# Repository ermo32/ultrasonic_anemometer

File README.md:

# Ultrasonic Anemometer

This project is about the development of an ultrasonic anemometer. Classical mechanical anemometers
has a disadvantage of a mechanical construction. This anemometer is based on the time of flight of
an ultrasonic pulse. 

## Getting Started

The project consists of a hardware and a software part. A microchip DSPIC33 is used as processing unit. On the board, the analog part consist of analog switches and 
operational amplifiers (OPAMPs).

### Prerequisities

What things you need to install the software and how to install them

```
Give examples
```

### Installing

A step by step series of examples that tell you have to get a development env running

Say what the step will be

```
Give the example
```

And repeat

```
until finished
```

End with an example of getting some data out of the system or using it for a little demo

## Running the tests

Explain how to run the automated tests for this system

### Break down into end to end tests

Explain what these tests test and why

```
Give an example
```

### And coding style tests

Explain what these tests test and why

```
Give an example
```

## Deployment

Add additional notes about how to deploy this on a live system

## Built With

* Dropwizard - Bla bla bla
* Maven - Maybe
* Atom - ergaerga

## Contributing

Please read [CONTRIBUTING.md](https://gist.github.com/PurpleBooth/b24679402957c63ec426) for details on our code of conduct, and the process for submitting pull requests to us.

## Versioning

We use [SemVer](http://semver.org/) for versioning. For the versions available, see the [tags on this repository](https://github.com/your/project/tags). 

## Authors

* **Billie Thompson** - *Initial work* - [PurpleBooth](https://github.com/PurpleBooth)

See also the list of [contributors](https://github.com/your/project/contributors) who participated in this project.

## License

This project is licensed under the MIT License - see the [LICENSE.md](LICENSE.md) file for details

## Acknowledgments

* Hat tip to anyone who's code was used
* Inspiration
* etc

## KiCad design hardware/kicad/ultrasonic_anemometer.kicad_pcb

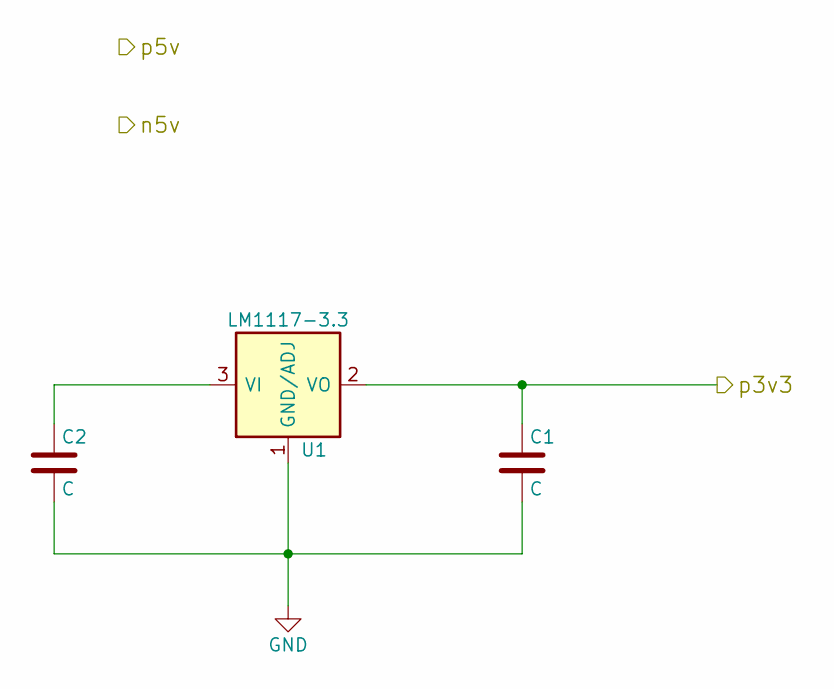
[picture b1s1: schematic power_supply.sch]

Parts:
C1, C2: C; C_0805_HandSoldering
U1: LM1117-3.3; SOT-223

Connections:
/Digital/p3v3: C1.1, U1.2 (VO), U1.4 (VO); also elsewhere on the board
GND: C1.2, C2.2, U1.1 (GND/ADJ); also elsewhere on the board
unnamed: C2.1, U1.3 (VI)

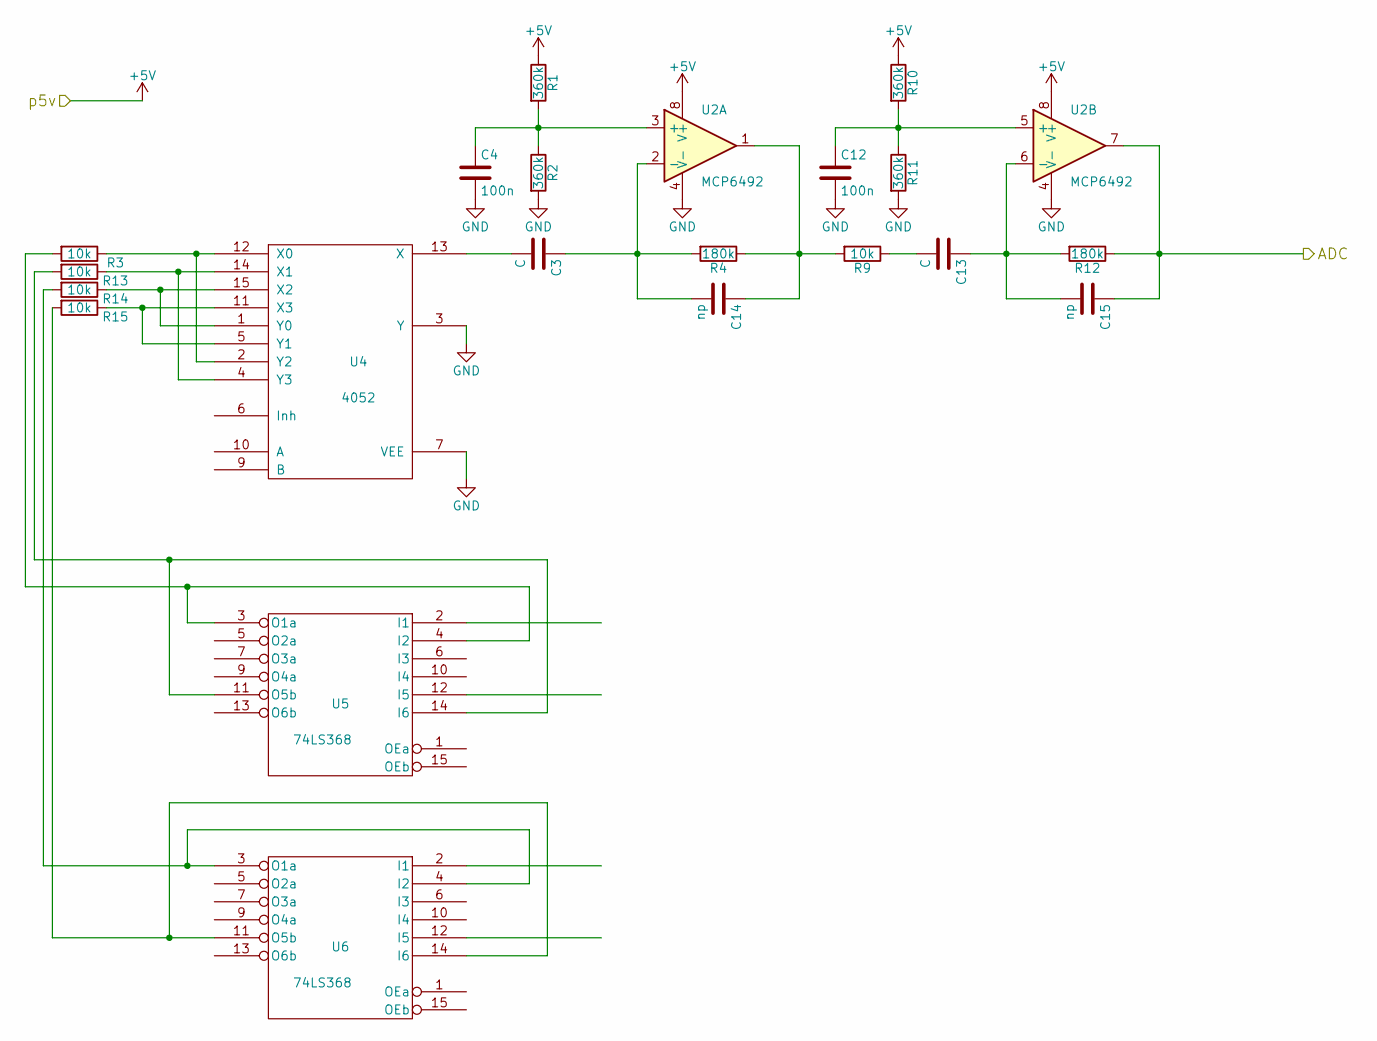
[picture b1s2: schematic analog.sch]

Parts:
C3, C13: C; C_0805_HandSoldering
C4, C12: 100n; C_0805_HandSoldering
C14, C15: np; C_0805_HandSoldering
R1, R2, R10, R11: 360k; R_0805_HandSoldering
R3, R9, R13, R14, R15: 10k; R_0805_HandSoldering
R4, R12: 180k; R_0805_HandSoldering
U2: MCP6492; SOIC-8_3.9x4.9mm_Pitch1.27mm
U4: 4052; DIP-16_W7.62mm_LongPads
U5, U6: 74LS368; DIP-16_W7.62mm_LongPads

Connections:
+5V: R1.1, R10.1, U2.8 (V+)
/Analog/ADC: C15.1, R12.1, U2.7; also elsewhere on the board
GND: C4.2, C12.2, R2.2, R11.2, U2.4 (V-), U4.3 (Y), U4.7 (VEE), U5.8 (GND), U6.8 (GND); also elsewhere on the board
unnamed: C3.2, U4.13 (X)
unnamed: C4.1, R1.2, R2.1, U2.3 (+)
unnamed: C12.1, R10.2, R11.1, U2.5 (+)
unnamed: C13.1, C15.2, R12.2, U2.6 (-)
unnamed: C13.2, R9.1
unnamed: C14.1, R4.1, R9.2, U2.1
unnamed: C3.1, C14.2, R4.2, U2.2 (-)
unnamed: R3.1, U4.2 (Y2), U4.12 (X0)
unnamed: R3.2, U5.3 (O1a), U5.4 (I2)
unnamed: R13.1, U4.4 (Y3), U4.14 (X1)
unnamed: R13.2, U5.11 (O5b), U5.14 (I6)
unnamed: R14.1, U4.1 (Y0), U4.15 (X2)
unnamed: R14.2, U6.3 (O1a), U6.4 (I2)
unnamed: R15.1, U4.5 (Y1), U4.11 (X3)
unnamed: R15.2, U6.11 (O5b), U6.14 (I6)
VCC: U5.16 (VCC), U6.16 (VCC)
VDD: U4.16 (VDD)
VSS: U4.8 (VSS)

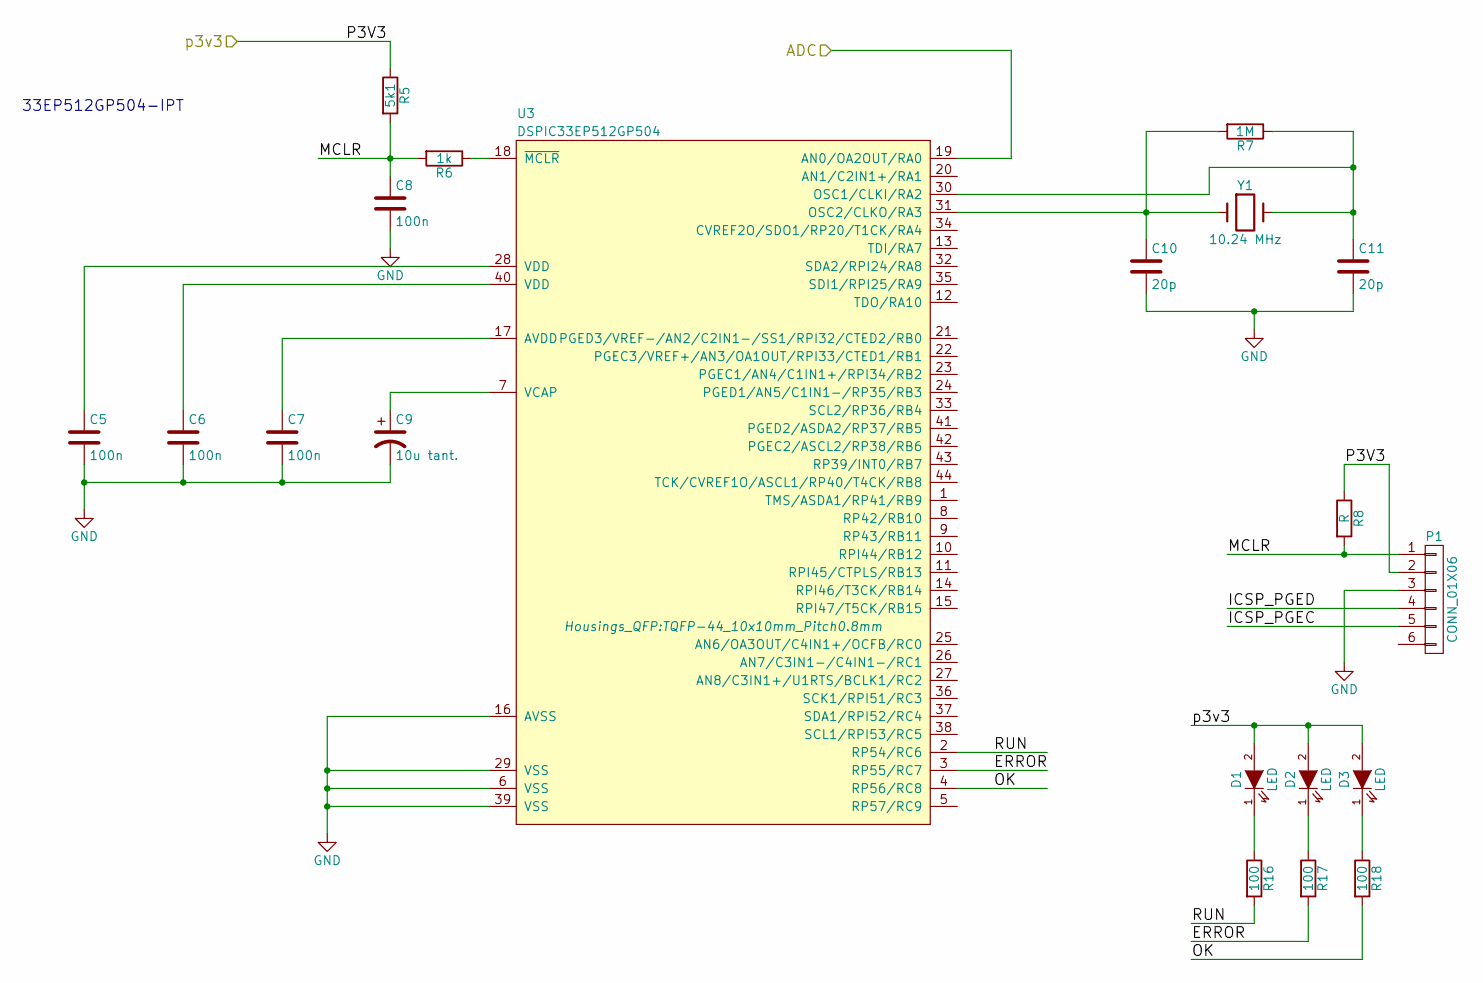
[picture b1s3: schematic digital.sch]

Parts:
C5, C6, C7, C8: 100n; C_0805_HandSoldering
C9: 10u tant.; SMD-1206_Pol
C10, C11: 20p; C_0805_HandSoldering
D1, D2, D3: LED; LED_0805
P1: CONN_01X06; Pin_Header_Straight_1x06
R5: 5k1; R_0805_HandSoldering
R6: 1k; R_0805_HandSoldering
R7: 1M; R_0805_HandSoldering
R8: R; R_0805_HandSoldering
R16, R17, R18: 100; R_0805_HandSoldering
U3: DSPIC33EP512GP504; TQFP-44_10x10mm_Pitch0.8mm
Y1: 10.24 MHz; Crystal_HC49-SD_SMD

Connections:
/Analog/ADC: U3.19 (AN0/OA2OUT/RA0); also elsewhere on the board
/Digital/ERROR: R17.2, U3.3 (RP55/RC7)
/Digital/ICSP_PGEC: P1.5
/Digital/ICSP_PGED: P1.4
/Digital/MCLR: C8.1, P1.1, R5.2, R6.2, R8.2
/Digital/OK: R18.2, U3.4 (RP56/RC8)
/Digital/RUN: R16.2, U3.2 (RP54/RC6)
/Digital/p3v3: D1.2 (A), D2.2 (A), D3.2 (A), P1.2, R5.1, R8.1; also elsewhere on the board
GND: C5.2, C6.2, C7.2, C8.2, C9.2, C10.2, C11.2, P1.3, U3.6 (VSS), U3.16 (AVSS), U3.29 (VSS), U3.39 (VSS); also elsewhere on the board
unnamed: C5.1, U3.28 (VDD)
unnamed: C6.1, U3.40 (VDD)
unnamed: C7.1, U3.17 (AVDD)
unnamed: C9.1, U3.7 (VCAP)
unnamed: C10.1, R7.2, U3.31 (OSC2/CLKO/RA3), Y1.1
unnamed: C11.1, R7.1, U3.30 (OSC1/CLKI/RA2), Y1.2
unnamed: D1.1 (K), R16.1
unnamed: D2.1 (K), R17.1
unnamed: D3.1 (K), R18.1
unnamed: R6.1, U3.18 (~MCLR)

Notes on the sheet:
33EP512GP504-IPT

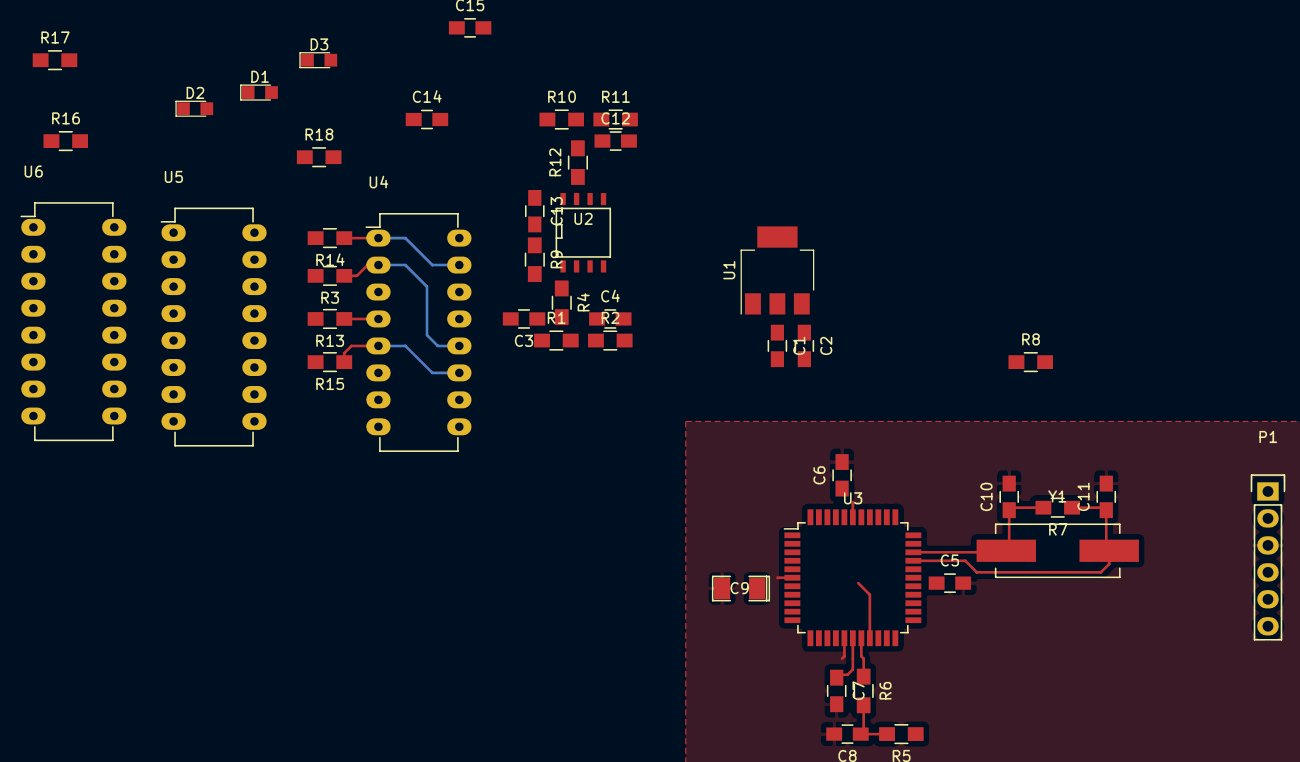
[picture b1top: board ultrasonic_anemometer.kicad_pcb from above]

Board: 2 copper layers, 44 parts (0 on the bottom side), 35 nets.

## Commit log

2016-10-09 Added git_commands.txt file
2016-10-09 Added selection guide.
2016-10-09 Added KiCAD project
2016-10-09 Added IPC pdf.
2016-10-09 Modified the README.md file.
2016-10-09 Added MPLAB project and datasheet.
2016-10-09 Update project
2016-10-09 Added sheets for KiCAD.
2016-10-09 Added Modex library and hierarchial sheets for power, analog and digital circuitry.
2016-10-09 Added datasheets.
2016-10-09 Added reference design.
2016-10-09 Added reference design
2016-10-11 Added paper with the cross correlation principle.
2016-10-12 Added datasheet from Murata about ultrasonic transducers.
2016-10-13 Added interesting datasheet from Texax Instruments.
2016-10-16 Added datasheet of the MCP6494 OPAMP
2016-10-16 Added ltspice simulation for analog ultrasonic amplifier.
2016-10-16 Updated LTSpice schematic.
2016-10-16 Updated schematic and Modex library.
2016-10-27 Added LTSPICE project for piezo acoustics.
2016-12-10 Added symbol for DSPIC
2016-12-10 Updated schematic and PCB.
2016-12-11 Updated schematic and PCB. Added OPAMP to the Modex library.
